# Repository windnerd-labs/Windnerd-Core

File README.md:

# WindNerd Core - Open Source Sensor & Development Board for 3D-Printed Anemometers

## Intro

The WindNerd Core is a **full magnetic** sensor board designed to fit inside the [**WindNerd 3D-printed-anemometer**](https://github.com/windnerd-labs/Anemometer-3D-files).

It is [**available as a kit**](https://windnerd.net/en/shop), which includes the board and essential parts like magnets and bearings.

You can use it as a dedicated wind **sensor module** for your weather station, or as an **Arduino compatible development board** that can, for example:

- Control peripherals such as a [LTE modem](examples/02-lte-modem-A7670X/) to send data remotely
- Drive LEDs that blink according to wind speed and direction
- Interface with other sensors (e.g., temperature, humidity, pressure)

For development, an ST-Link V2 (or compatible) dongle is recommended. However, alternative firmwares can also be uploaded via a serial bootloader.

## Factory Firmware

The board is shipped with factory firmware that outputs instant wind values and averaged wind values over a serial connection.

The average power consumption is only **0.6mA** (3.3V or 5V).

It can be connected to a computer using a **USB-serial-TTL adapter** or to any MCU board that provides a **UART serial interface**.

The baudrate is 9600bps 8N1. This configuration allows fairly long wiring, e.g. to reach the top of a pole.  

Two types of messages are provided, the default speed unit is km/h and values are averaged for the last 10 minutes:  

**Instant wind** (every 3 Sec)

`WNI,<speed>,<direction 0-359>`
ex: `WNI,10.4,149`  

**Average wind report** (every minute)

`WNA,<speed avg>,<direction avg 0-359>,<min speed>,<max speed>`
ex: `WNA,12.2,93,0,21.4`  

The factory firmware is based on an [Arduino example sketch](examples/01-factory-v1/01-factory-v1.ino) that can be easily tweaked to your own needs.

[**How to read serial data from another device**](docs/READSERIAL.md)

## Arduino library

This repository provides an Arduino library that implements a driver for the magnetic sensors and computes wind speed and direction, exposing the values through a simple API.

[**How to install WindNerd Core library and program the board**](docs/PROGRAM.md)

[**WindNerd Core API reference**](docs/API-REFERENCE.md)

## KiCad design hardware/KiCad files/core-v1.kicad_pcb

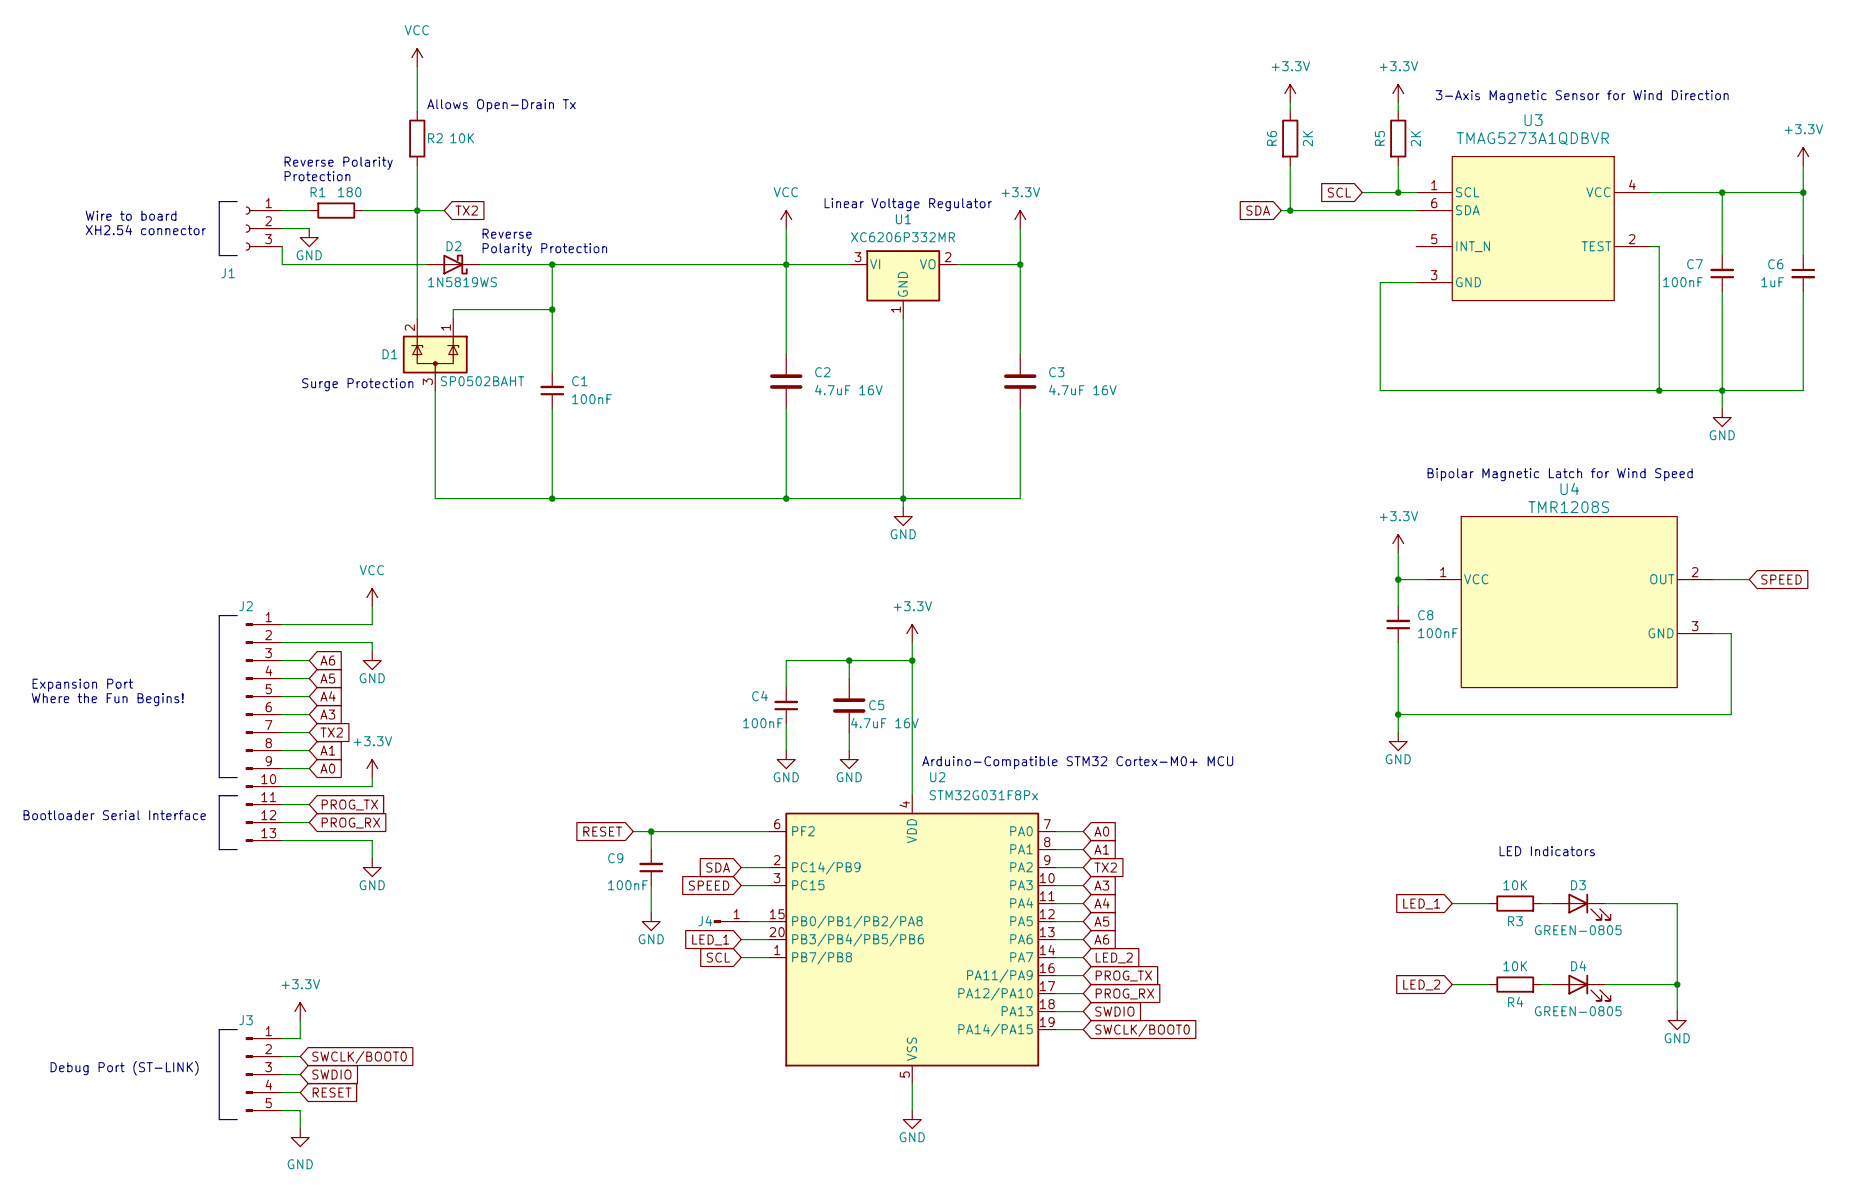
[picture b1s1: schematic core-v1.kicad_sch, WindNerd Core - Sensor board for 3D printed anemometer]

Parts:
C1, C4, C7, C8, C9: 100nF; C_0603_1608Metric
C2, C3, C5: 4.7uF 16V; C_0603_1608Metric
C6: 1uF; C_0603_1608Metric
D1: SP0502BAHT; SOT-23
D2: 1N5819WS; D_SOD-323
D3, D4: GREEN-0805; LED_0805_2012Metric
J1: XH2.54-3P SMD; ZX-XH2.54-3
J2: Conn_01x13_Pin; PinHeader_1x13_P2.54mm_Vertical
J3: Conn_01x05_Pin; PinHeader_1x05_P2.54mm_Vertical
J4: Conn_01x01_Pin; PinHeader_1x01_P2.54mm_Vertical
R1: 180; R_1206_3216Metric
R2, R3, R4: 10K; R_0603_1608Metric
R5, R6: 2K; R_0603_1608Metric
U1: XC6206P332MR; SOT-23-3
U2: STM32G031F8Px; TSSOP-20_4.4x6.5mm_P0.65mm
U3: TMAG5273A1QDBVR; SOT-23-6
U4: TMR1208S; SOT-23

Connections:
+3.3V: C3.1, C4.2, C5.1, C6.1, C7.2, C8.2, J2.10, J3.1, R5.1, R6.1, U1.2 (VO), U2.4 (VDD), U3.4 (VCC), U4.1 (VCC)
A0: J2.9, U2.7 (PA0)
A1: J2.8, U2.8 (PA1)
A3: J2.6, U2.10 (PA3)
A4: J2.5, U2.11 (PA4)
A5: J2.4, U2.12 (PA5)
A6: J2.3, U2.13 (PA6)
GND: C1.1, C2.2, C3.2, C4.1, C5.2, C6.2, C7.1, C8.1, C9.1, D1.3 (A), D3.1 (K), D4.1 (K), J1.2, J2.2, J2.13, J3.5, U1.1 (GND), U2.5 (VSS), U3.2 (TEST), U3.3 (GND), U4.3 (GND)
LED_1: R3.1, U2.20 (PB3/PB4/PB5/PB6)
LED_2: R4.1, U2.14 (PA7)
unnamed: D2.2 (A), J1.3
unnamed: D3.2 (A), R3.2
unnamed: D4.2 (A), R4.2
unnamed: J1.1, R1.2
unnamed: J4.1, U2.15 (PB0/PB1/PB2/PA8)
PROG_RX: J2.12, U2.17 (PA12/PA10)
PROG_TX: J2.11, U2.16 (PA11/PA9)
RESET: C9.2, J3.4, U2.6 (PF2)
SCL: R5.2, U2.1 (PB7/PB8), U3.1 (SCL)
SDA: R6.2, U2.2 (PC14/PB9), U3.6 (SDA)
SPEED: U2.3 (PC15), U4.2 (OUT)
SWCLK/BOOT0: J3.2, U2.19 (PA14/PA15)
SWDIO: J3.3, U2.18 (PA13)
TX2: D1.2 (K), J2.7, R1.1, R2.2, U2.9 (PA2)
VCC: C1.2, C2.1, D1.1 (K), D2.1 (K), J2.1, R2.1, U1.3 (VI)

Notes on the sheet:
3-Axis Magnetic Sensor for Wind Direction
Bipolar Magnetic Latch for Wind Speed
Linear Voltage Regulator
Wire to board XH2.54 connector
Bootloader Serial Interface
Reverse Polarity Protection
Surge Protection
Expansion Port Where the Fun Begins!
Arduino-Compatible STM32 Cortex-M0+ MCU
Debug Port (ST-LINK)
Allows Open-Drain Tx
Reverse Polarity Protection
LED Indicators

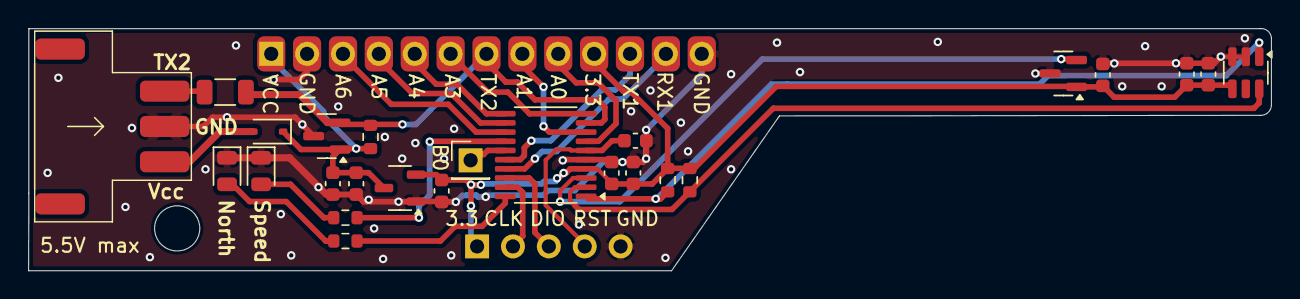
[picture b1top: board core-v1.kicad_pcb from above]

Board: 2 copper layers, 88.0 x 17.1 mm, 27 parts (0 on the bottom side), 25 nets.

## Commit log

2025-10-02 initial
2025-10-03 docs, function renaming
2025-10-03 better images
2025-10-03 improve readme
2025-10-11 Initial plan
2025-10-11 Add Luat Air780E 4G integration example and documentation
2025-10-11 Add comprehensive testing checklist for 4G integration
2025-10-11 Add implementation summary documentation
2025-10-11 Add Windguru API integration to 4G example
2025-10-11 Update documentation for Windguru API integration
2025-10-11 Update example README with Windguru setup instructions
2025-10-13 drop sample when tick missed
2025-10-13 add read serial snippets
2025-10-13 library properties
2025-10-13 match library name with headers filename
2025-10-30 board selection screenshots
2025-10-30 board selection correction
2025-10-30 fix TMAG sleep
2025-10-30 low power mode
2025-10-30 1.1.0
2025-10-30 breezedude sketch
2025-10-31 TIME_BEFORE_LOW_POWER
2025-10-31 type renaming, computeReportForPeriodInSecIndexedFromLast(), getSampleIndexedFromLast
2025-10-31 1.2.0
2025-11-01 new sample type name
2025-11-01 at modem blind control
2025-11-06 unique endpoint
2025-11-07 fix sleep skipping
2025-11-10 LTE modem readme
2025-11-10 remove arduihno lint
2025-11-10 fix readme
2025-11-10 LTE modem
2025-11-10 link to LTE modem example
2025-11-10 fix link
2025-11-10 1.3.0
2025-12-06 bme280
2025-12-06 terminate http session at beginning of cycle
2025-12-15 LTE + BME280
2026-02-04 Add air780e 4G example with windguru knots conversion and security cleanup
    - Add complete Air780E STM32G0 4G module example (air780e.ino)
    - Windguru API integration with dual upload support (WTP + Windguru)
    - Wind speed conversion: knots for Windguru, m/s for Windnerd
    - Security: Replace hardcoded credentials with placeholders
    - Features: Independent watchdog, state timeout, periodic modem reset, ultra-low power mode
    - Includes MD5 support for Windguru authentication hash
2026-02-04 Add Air780E 4G example with Windguru knots conversion
    - Production-ready Air780E STM32G0 firmware with dual upload support
    - Windguru API integration: converts wind speed to knots (1 m/s = 1.94384 knots)
    - Windnerd WTP: maintains wind data in m/s
    - Features: non-blocking state machine, watchdog, state timeout, periodic modem reset
    - Ultra-low power mode for battery-powered deployments
    - MD5 authentication support for Windguru API
2026-02-04 Remove old 4g-air780e example (replaced by production air780e)
2026-02-04 Add compile_flash.sh script and air780e production example
2026-02-04 Keep only air780e README documentation
2026-02-23 nmea0183 example
2026-03-05 alt pins attribution, alt frequency to wind speedd ratio
2026-03-06 wtp temp limits
2026-03-06 wtp payload helper
2026-03-07 fix voltage decimal
2026-03-07 update A7670X example
2026-03-07 STM32CubeProgrammer installation
2026-03-07 fix modem reboot
2026-03-08 don't reboot at post_cnt 0
2026-03-08 serial debug init
2026-03-10 hint invertVanePolarity
2026-03-10 bme280 lib requirement
2026-03-10 1.4.0
2026-03-14 add apn
2026-03-15 readme apn
2026-03-15 1.4.1
2026-04-10 data consumption
2026-04-10 API reference
2026-04-30 bitbang i2c when transmission error
2026-05-02 wtp temp_in, meta + doc fix
2026-05-02 1.5.0
2026-05-18 leds open drain option
2026-05-27 reject any impossible speed pulse
2026-05-27 split I2C
2026-05-30 wtp payload always m/s
2026-06-01 1.6.0

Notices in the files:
hardware/KiCad files/core-v1.kicad_pcb:
Copyright (c) 2025 windnerd.net
Licensed under CERN Open Hardware License V2 – Strongly Reciprocal (CERN-OHL-S)
